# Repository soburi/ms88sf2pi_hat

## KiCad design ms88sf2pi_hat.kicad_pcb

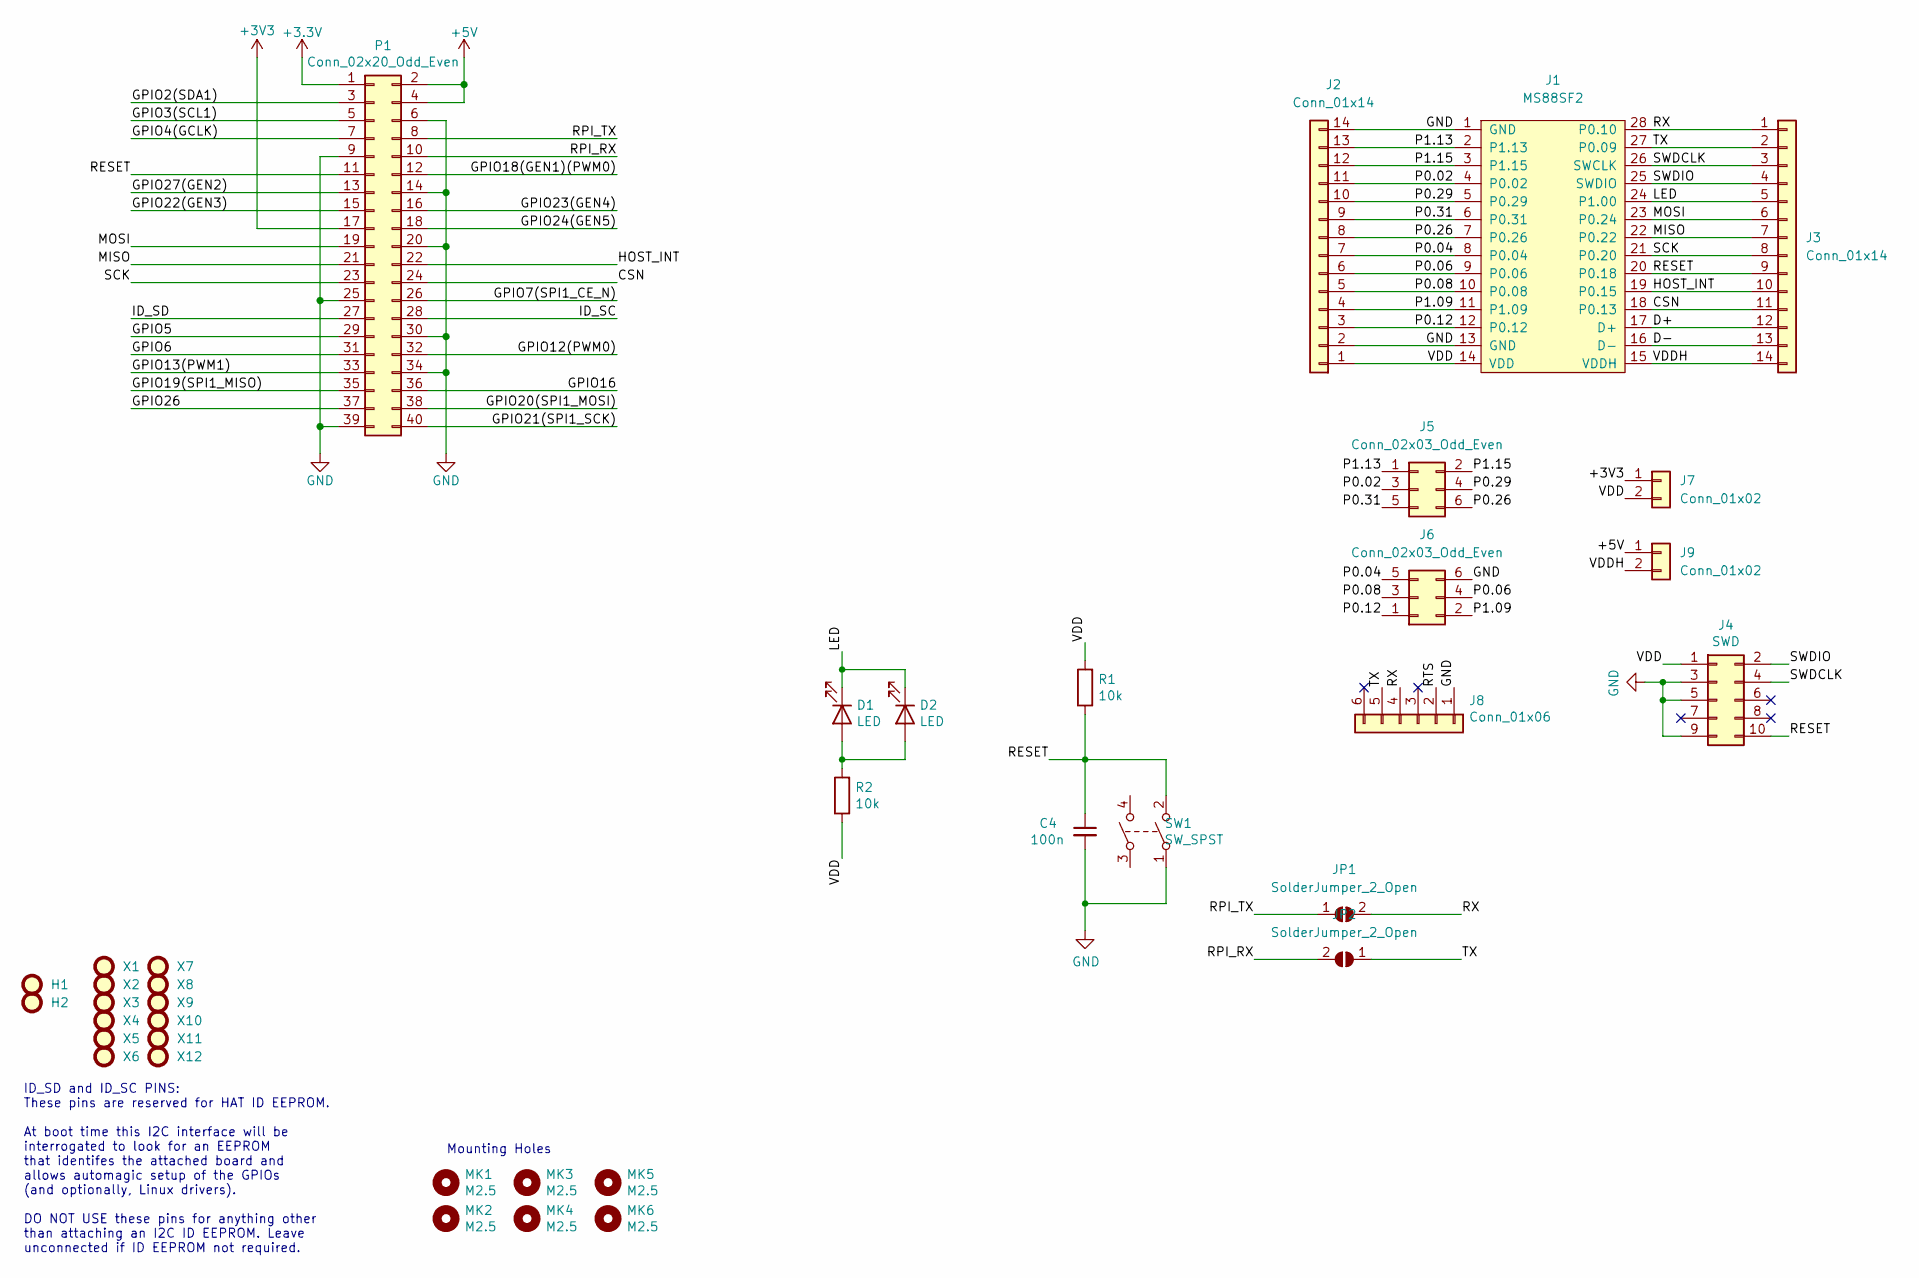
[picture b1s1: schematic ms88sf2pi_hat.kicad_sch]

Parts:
C4: 100n; C_Disc_D3.0mm_W1.6mm_P2.50mm
D1: LED; LED_1206_3216Metric_Pad1.42x1.75mm_HandSolder
D2: LED; LED_D3.0mm
H1, H2: 1mm-hole
J1: MS88SF2
J2, J3: Conn_01x14; PinSocket_1x14_P2.54mm_Vertical
J4: SWD; PinHeader_2x05_P1.27mm_Vertical_SMD
J5, J6: Conn_02x03_Odd_Even; PinHeader_2x03_P2.54mm_Vertical
J7, J9: Conn_01x02; PinHeader_1x02_P2.54mm_Vertical
J8: Conn_01x06; PinHeader_1x06_P2.54mm_Vertical
JP1, JP2: SolderJumper_2_Open; SolderJumper-2_P1.3mm_Open_TrianglePad1.0x1.5mm
MK1, MK2, MK3, MK4, MK5, MK6: M2.5; MountingHole_2.7mm_M2.5
P1: Conn_02x20_Odd_Even; PinSocket_2x20_P2.54mm_Vertical
R1, R2: 10k; R_Axial_DIN0207_L6.3mm_D2.5mm_P7.62mm_Horizontal
SW1: SW_SPST; SKRPACE010
X1, X2, X4, X6, X8: Universal_D2.0mm_Drill0.9mm_4x3
X3, X5, X7, X9: Universal_D2.0mm_Drill0.9mm_4x4
X10, X11, X12: Universal_D2.0mm_Drill0.9mm_2x2

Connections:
+5V: J9.1, P1.2, P1.4
/CSN: J1.18 (P0.13), J3.11, P1.24
/D+: J1.17 (D+), J3.12
/D-: J1.16 (D-), J3.13
/GPIO2(SDA1): P1.3
/GPIO3(SCL1): P1.5
/GPIO4(GCLK): P1.7
/GPIO5: P1.29
/GPIO6: P1.31
/GPIO7(SPI1_CE_N): P1.26
/GPIO12(PWM0): P1.32
/GPIO13(PWM1): P1.33
/GPIO16: P1.36
/GPIO18(GEN1)(PWM0): P1.12
/GPIO19(SPI1_MISO): P1.35
/GPIO20(SPI1_MOSI): P1.38
/GPIO21(SPI1_SCK): P1.40
/GPIO22(GEN3): P1.15
/GPIO23(GEN4): P1.16
/GPIO24(GEN5): P1.18
/GPIO26: P1.37
/GPIO27(GEN2): P1.13
/HOST_INT: J1.19 (P0.15), J3.10, P1.22
/ID_SC: P1.28
/ID_SD: P1.27
/LED: D1.1 (K), D2.1 (K), J1.24 (P1.00), J3.5
/MISO: J1.22 (P0.22), J3.7, P1.21
/MOSI: J1.23 (P0.24), J3.6, P1.19
/P0.02: J1.4 (P0.02), J2.11, J5.3
/P0.04: J1.8 (P0.04), J2.7, J6.5
/P0.06: J1.9 (P0.06), J2.6, J6.4
/P0.08: J1.10 (P0.08), J2.5, J6.3
/P0.12: J1.12 (P0.12), J2.3, J6.1
/P0.26: J1.7 (P0.26), J2.8, J5.6
/P0.29: J1.5 (P0.29), J2.10, J5.4
/P0.31: J1.6 (P0.31), J2.9, J5.5
/P1.09: J1.11 (P1.09), J2.4, J6.2
/P1.13: J1.2 (P1.13), J2.13, J5.1
/P1.15: J1.3 (P1.15), J2.12, J5.2
/RESET: C4.1, J1.20 (P0.18), J3.9, J4.10, P1.11, R1.1, SW1.2
/RPI_RX: JP2.2 (B), P1.10
/RPI_TX: JP1.1 (A), P1.8
/RTS: J8.2
/RX: J1.28 (P0.10), J3.1, J8.4, JP1.2 (B)
/SCK: J1.21 (P0.20), J3.8, P1.23
/SWDCLK: J1.26 (SWCLK), J3.3, J4.4
/SWDIO: J1.25 (SWDIO), J3.4, J4.2
/TX: J1.27 (P0.09), J3.2, J8.5, JP2.1 (A)
/VDD: J1.14 (VDD), J2.1, J4.1, J7.2, R1.2, R2.1
/VDDH: J1.15 (VDDH), J3.14, J9.2
GND: C4.2, J1.1 (GND), J1.13 (GND), J2.2, J2.14, J4.3, J4.5, J4.9, J6.6, J8.1, P1.6, P1.9, P1.14, P1.20, P1.25, P1.30, P1.34, P1.39, SW1.1
unnamed: D1.2 (A), D2.2 (A), R2.2

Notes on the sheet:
ID_SD and ID_SC PINS: These pins are reserved for HAT ID EEPROM. At boot time this I2C interface will be interrogated to look for an EEPROM that identifes the attached board and allows automagic setup of the GPIOs (and optionally, Linux drivers). DO NOT USE these pins for anything other than attach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
Mounting Holes

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
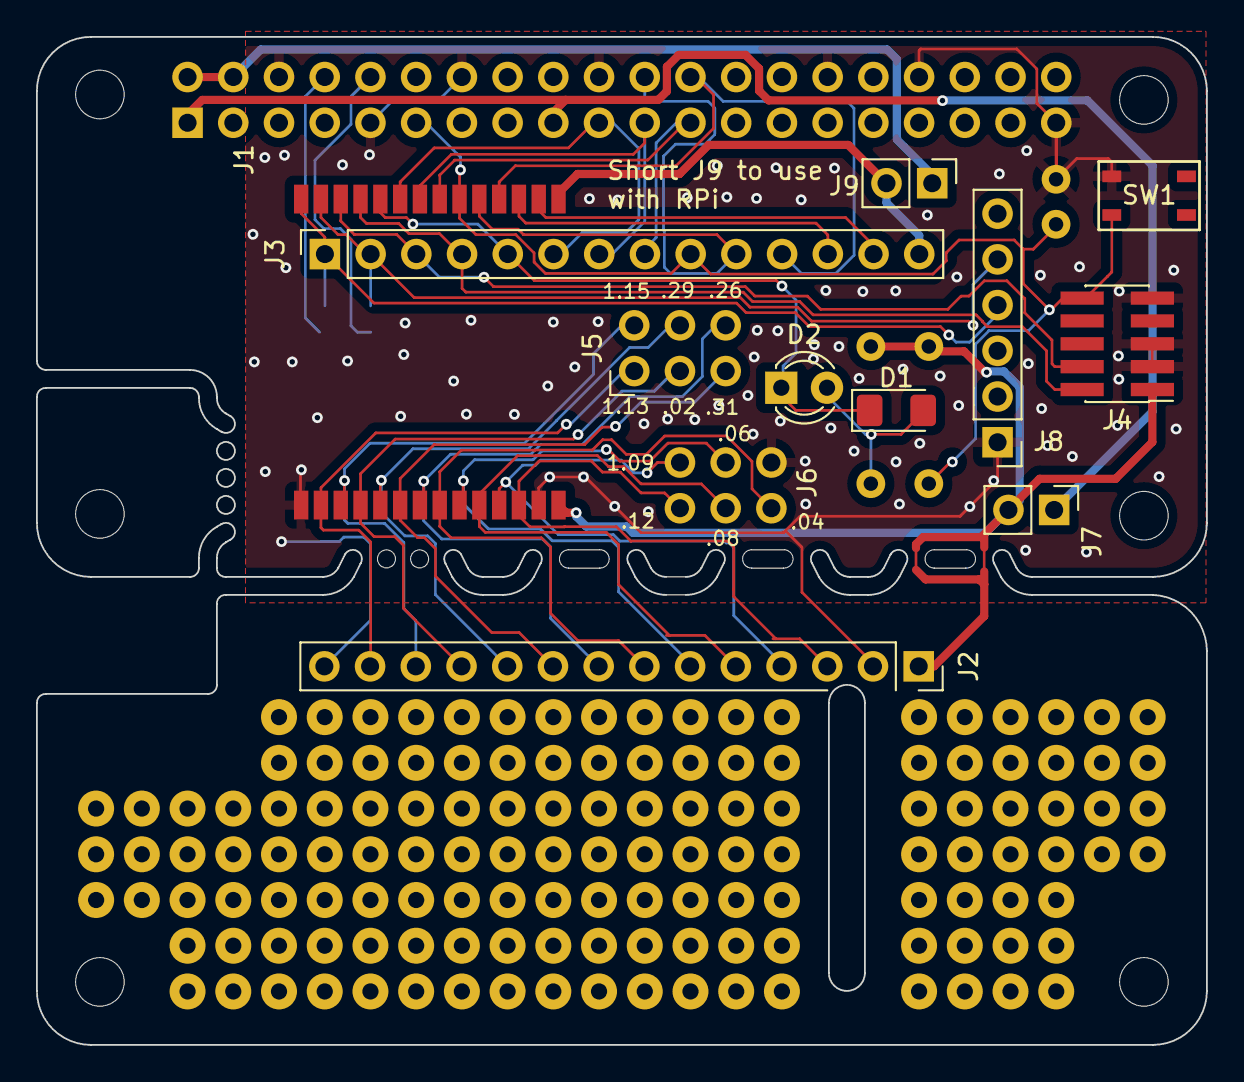
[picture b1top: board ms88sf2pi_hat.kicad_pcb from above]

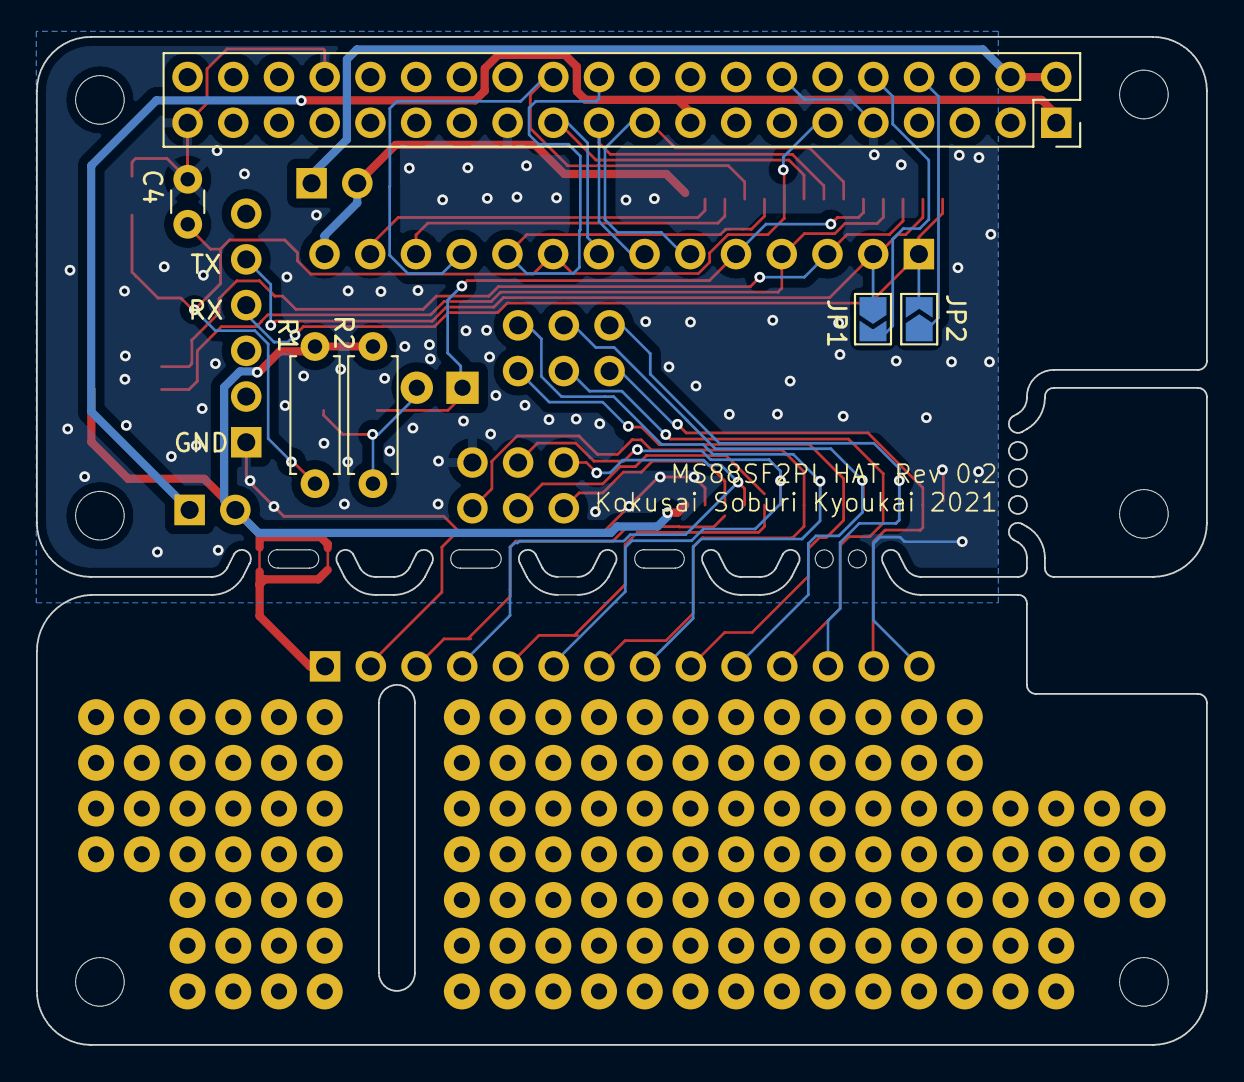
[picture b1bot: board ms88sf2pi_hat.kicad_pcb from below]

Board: 2 copper layers, 65.0 x 56.0 mm, 38 parts (6 on the bottom side), 32 nets.
